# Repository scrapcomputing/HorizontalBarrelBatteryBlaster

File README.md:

# Horizontal Barrel Battery Blaster

Horizontal Barrel Battery Blaster is a small PCB for replacing an old rechargeable barrel-type CMOS batteries with a non-rechargeable CR2032 Lithium battery.
Such barrel batteries were quite common on vintage computer motherboards up until the 486 era.
These barrel batteries tend to leak, damaging the motherboard and the surrounding components.

Unlike the [Barrel Battery Blaster](https://github.com/scrapcomputing/BarrelBatteryBlaster) and the [Vertical Battery Blaster](https://github.com/scrapcomputing/VerticalBarrelBatteryBlaster) this board sits horizontally on the motherboard.

> **Warning**
> There may not be enough clearance on your motherboard for this board and the CR2032 holder. So please check!

# Features
- Uses a standard through-hole CR2032 battery holder of the horizontal type
- Accepts 3 types of diode footprints: through-hole (e.g., 1N5817), 1206 and SOT23 ANK (e.g., BAS40-04)
- Rev.0.2. includes solder pads for a MAX40200 SOT23-5 ideal diode. This is great for older systems that need as little voltage drop as possible.

# Video
https://www.youtube.com/watch?v=v_9UKSxLt-k

# Similar Projects
- [Vertical Battery Blaster](https://github.com/scrapcomputing/VerticalBarrelBatteryBlaster)
- [Barrel Battery Blaster](https://github.com/scrapcomputing/BarrelBatteryBlaster)
- [Not-A-Varta](https://github.com/wiretap-retro/Not-A-Varta-CR2032)

# How can I get one?

You can order one at your PCB fab of choice.
The simplest way is to use the zipped gerber file found in the [releases](https://github.com/scrapcomputing/HorizontalBarrelBatteryBlaster/releases).

# Bill of materials

Item                                             | #   | Description
-------------------------------------------------|-----|-----------------------------------------
Pins out of an male header (usually 2.54mm pitch)| 2   | For connecting the BarrelBatteryBlaster to the motherboard
Horizontally mounted CR2032 battery holder       | 1   | For the CR2032 Lithium battery
Diode or Ideal diode                             | 1   | Through-hole (e.g., 1N5817) or 1206 or SOT23 ANK (current flows pin1 -> pin3 like in BAS40 or BAS40-04) or MAX40200 SOT23-5 ideal didoe

# Changelist
rev.0.1: Original revision 
rev.0.2: Adds solder pads for MAX40200 ideal diode

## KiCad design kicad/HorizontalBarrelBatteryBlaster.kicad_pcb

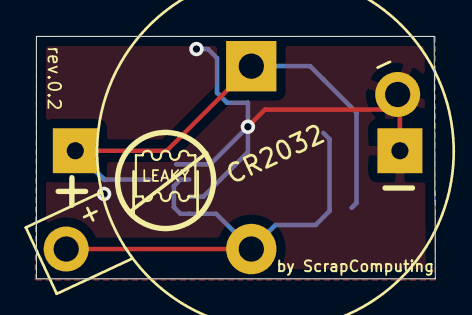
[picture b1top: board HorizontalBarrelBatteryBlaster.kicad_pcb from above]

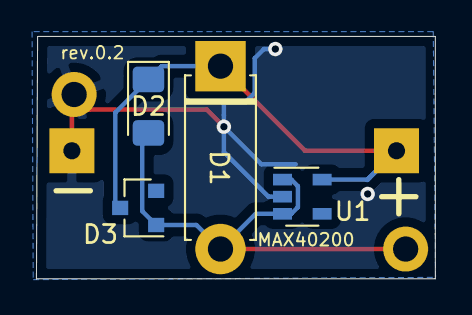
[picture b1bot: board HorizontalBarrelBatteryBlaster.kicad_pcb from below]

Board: 2 copper layers, 22.2 x 13.5 mm, 6 parts (5 on the bottom side), 3 nets.

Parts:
BarrelBattery1: BarrelBattery; BarrelBattery_pads
CR2032: CR2032; CR2032_battery_holder
D1: D_Schottky; D_5W_P10.16mm_Horizontal
D2: D_Schottky; D_1206_3216Metric_Pad1.42x1.75mm_HandSolder
D3: D_Schottky; D_SOT-23_ANK
U1: MAX40200AUK; SOT-23-5

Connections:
/3V: CR2032.1, D1.2, D2.2, D3.2, U1.1, U1.3
GND: BarrelBattery1.2, CR2032.2, U1.2
unnamed: BarrelBattery1.1, D1.1, D2.1, D3.1, U1.5

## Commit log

2023-11-06 Improve README
2023-11-06 Includes solder pads for MAX40200 ideal diode
